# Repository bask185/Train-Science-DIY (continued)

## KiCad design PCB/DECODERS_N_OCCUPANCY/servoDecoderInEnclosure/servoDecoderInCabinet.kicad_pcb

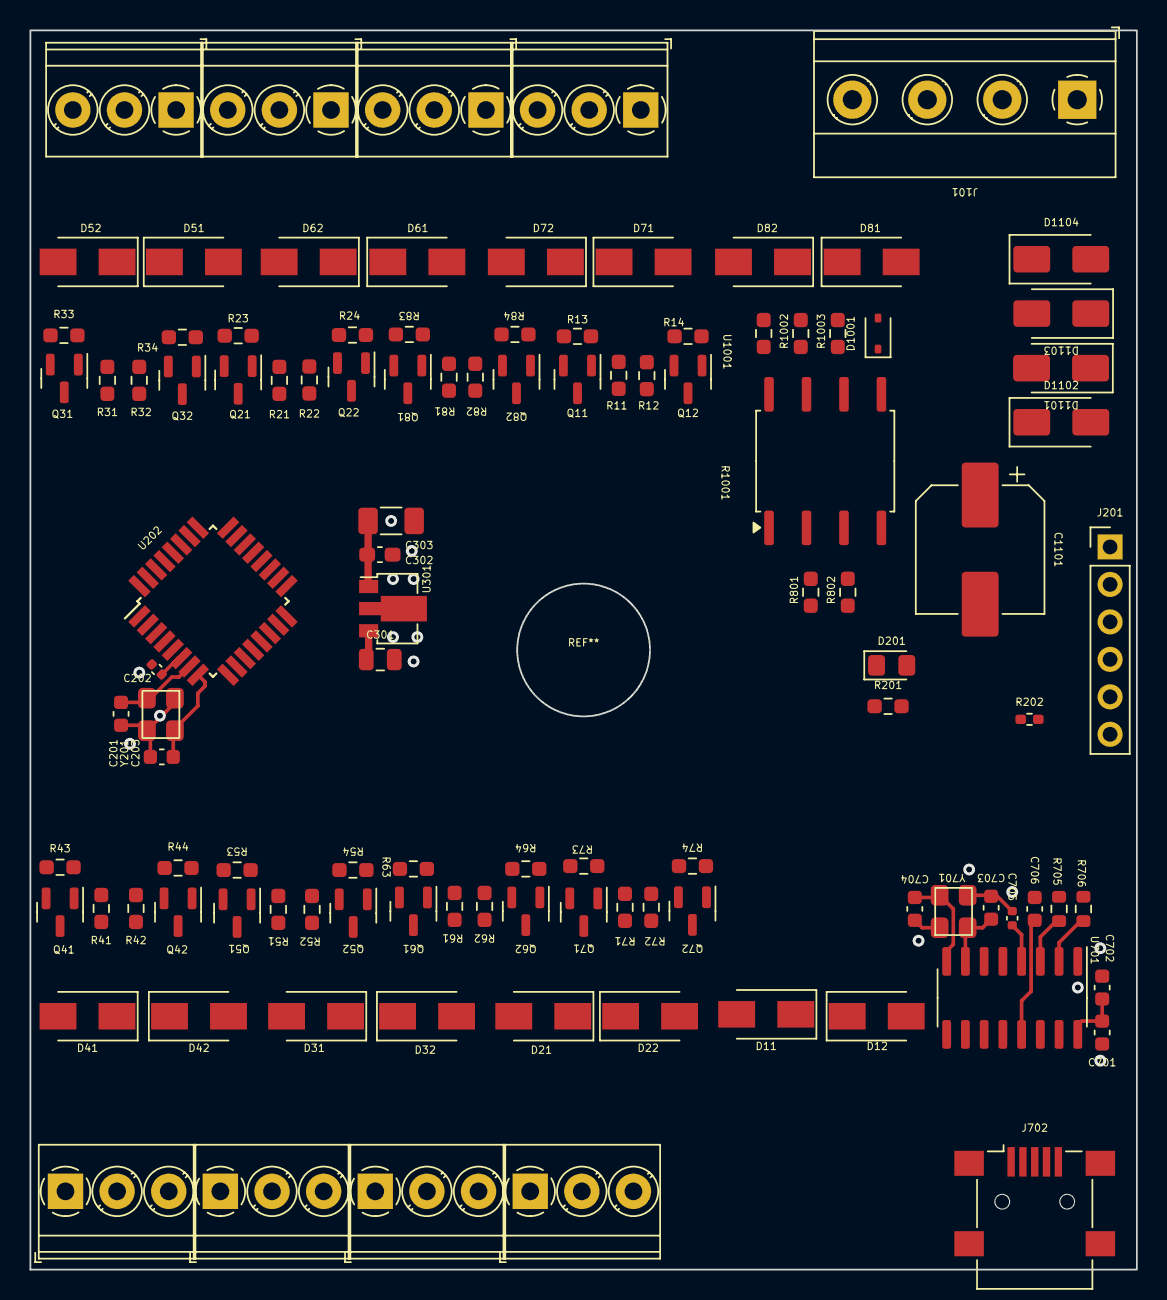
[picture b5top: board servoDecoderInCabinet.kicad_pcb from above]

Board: 2 copper layers, 75.0 x 84.0 mm, 101 parts (0 on the bottom side), 29 nets.

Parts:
C201, C203: 12pF; C_0603_1608Metric
C202, C705: 100nF; C_0402_1005Metric
C301: 470nF; C_0805_2012Metric
C302: 100nF; C_0603_1608Metric_Pad1.08x0.95mm_HandSolder
C303: 100uF; C_1206_3216Metric_Pad1.33x1.80mm_HandSolder
C701: 10uF; C_0603_1608Metric
C702, C706: 100nF; C_0603_1608Metric
C703, C704: 22pF; C_0603_1608Metric
C1101: 1000uF; CP_Elec_8x10.5
D11, D12, D21, D22, D31, D32, D41, D42, D51, D52, D61, D62, D71, D72, D81, D82: D_SMA
D201: LED; LED_0805_2012Metric_Pad1.15x1.40mm_HandSolder
D1001: 1N4148WS; D_SOD-323
D1101, D1102, D1103, D1104: SS53; D_SMA
J101: Screw_Terminal_01x04; TerminalBlock_Phoenix_MKDS-1,5-4-5.08_1x04_P5.08mm_Horizont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
J201: ICSP; PinHeader_1x06_P2.54mm_Vertical
J702: USB_B_Mini; USB_Mini-B_Lumberg_2486_01_Horizontal
Q11, Q12, Q21, Q22, Q31, Q32, Q41, Q42, Q51, Q52, Q61, Q62, Q71, Q72, Q81, Q82: SOT-23
R11, R12, R13, R14, R21, R22, R23, R24, R31, R32, R33, R34, R41, R42, R43, R44, R51, R52, R53, R54, R61, R62, R63, R64, R71, R72, R73, R74, R81, R82, R83, R84: R_0603_1608Metric_Pad0.98x0.95mm_HandSolder
R201: 6k2; R_0603_1608Metric_Pad0.98x0.95mm_HandSolder
R202: 10k; R_0402_1005Metric_Pad0.72x0.64mm_HandSolder
R705, R706: 1k; R_0603_1608Metric
R801, R802, R1002, R1003: 10k; R_0603_smalltext
R1001: 1k; R_0603_smalltext
U202: ATmega328-A; TQFP-32_7x7mm_P0.8mm
U301: L78L05_SOT89; SOT-89-3
U701: CH340G; SOIC-16_3.9x9.9mm_P1.27mm
U1001: 6N137; SOP-8_6.62x9.15mm_P2.54mm
Y201: Crystal_GND2; crystal_arduino
Y701: Crystal; crystal_arduino

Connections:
+5V: C202.1, C302.1, C303.1, C701.1, C702.1, J201.2, J702.1 (VBUS), R201.1, R202.2, R801.2, R802.2, R1002.1, R1003.1, U202.4 (VCC), U202.6 (VCC), U202.18 (AVCC), U301.1 (OUT), U701.16 (VCC), U1001.8 (VCC)
/A: J101.4, R1001.1
/B: D1001.2 (A), J101.3, U1001.3 (C)
/Buck/VCC: C301.1, C1101.1, D1101.1 (K), D1103.1 (K), U301.3 (IN)
/DCC/DCC_TTL: R1003.2, U202.32 (PD2), U1001.6 (VO)
/D_bridge/AC_1: D1101.2 (A), D1102.1 (K), J101.2
/D_bridge/AC_2: D1103.2 (A), D1104.1 (K), J101.1
/USB/Reset: C706.2, J201.6, R202.1, U202.29 (~RESET/PC6)
/USB/Rx: R705.2, U202.30 (PD0)
/USB/Tx: R706.1, U202.31 (PD1)
/atmega/LED: D201.1 (K), J201.3, U202.17 (PB5)
/atmega/X1: C201.2, U202.7 (XTAL1/PB6), Y201.1
/atmega/X2: C203.2, U202.8 (XTAL2/PB7), Y201.3
/atmega/bus2.pin1: R801.1, U202.11 (PD7)
/atmega/bus2.pin2: R802.1, U202.24 (PC1)
/atmega/sw3: J201.5, U202.15 (PB3)
/atmega/sw4: J201.4, U202.16 (PB4)
GND: C201.1, C202.2, C203.1, C301.2, C302.2, C303.2, C701.2, C702.2, C703.2, C704.2, C705.1, C1101.2, D1102.2 (A), D1104.2 (A), J201.1, J702.5 (GND), J702.6 (Shield), Q11.2 (S), Q12.2 (S), Q21.2 (S), Q22.2 (S), Q31.2 (S), Q32.2 (S), Q41.2 (S), Q42.2 (S), Q51.2 (S), Q52.2 (S), Q61.2 (S), Q62.2 (S), Q71.2 (S), Q72.2 (S), Q81.2 (S), Q82.2 (S), R13.1, R14.1, R23.1, R24.1, R33.1, R34.1, R43.1, R44.1, R53.1, R54.1, R63.1, R64.1, R73.1, R74.1, R83.1, R84.1, U202.3 (GND), U202.5 (GND), U202.21 (GND), U301.2 (GND), U701.1 (GND), U1001.5 (GND), Y201.2 (GND), Y201.4 (GND), Y701.2 (GND), Y701.4 (GND)
unnamed: D201.2 (A), R201.2
unnamed: D1001.1 (K), R1001.2, U1001.2 (A)
unnamed: J702.3 (D+), U701.5 (UD+)
unnamed: J702.2 (D-), U701.6 (UD-)
unnamed: R706.2, U701.3 (RXD)
unnamed: R705.1, U701.2 (TXD)
unnamed: C705.2, U701.4 (V3)
unnamed: C703.1, U701.7 (XI), Y701.1
unnamed: C704.1, U701.8 (XO), Y701.3
unnamed: C706.1, U701.13 (~DTR)
unnamed: R1002.2, U1001.7 (EN)

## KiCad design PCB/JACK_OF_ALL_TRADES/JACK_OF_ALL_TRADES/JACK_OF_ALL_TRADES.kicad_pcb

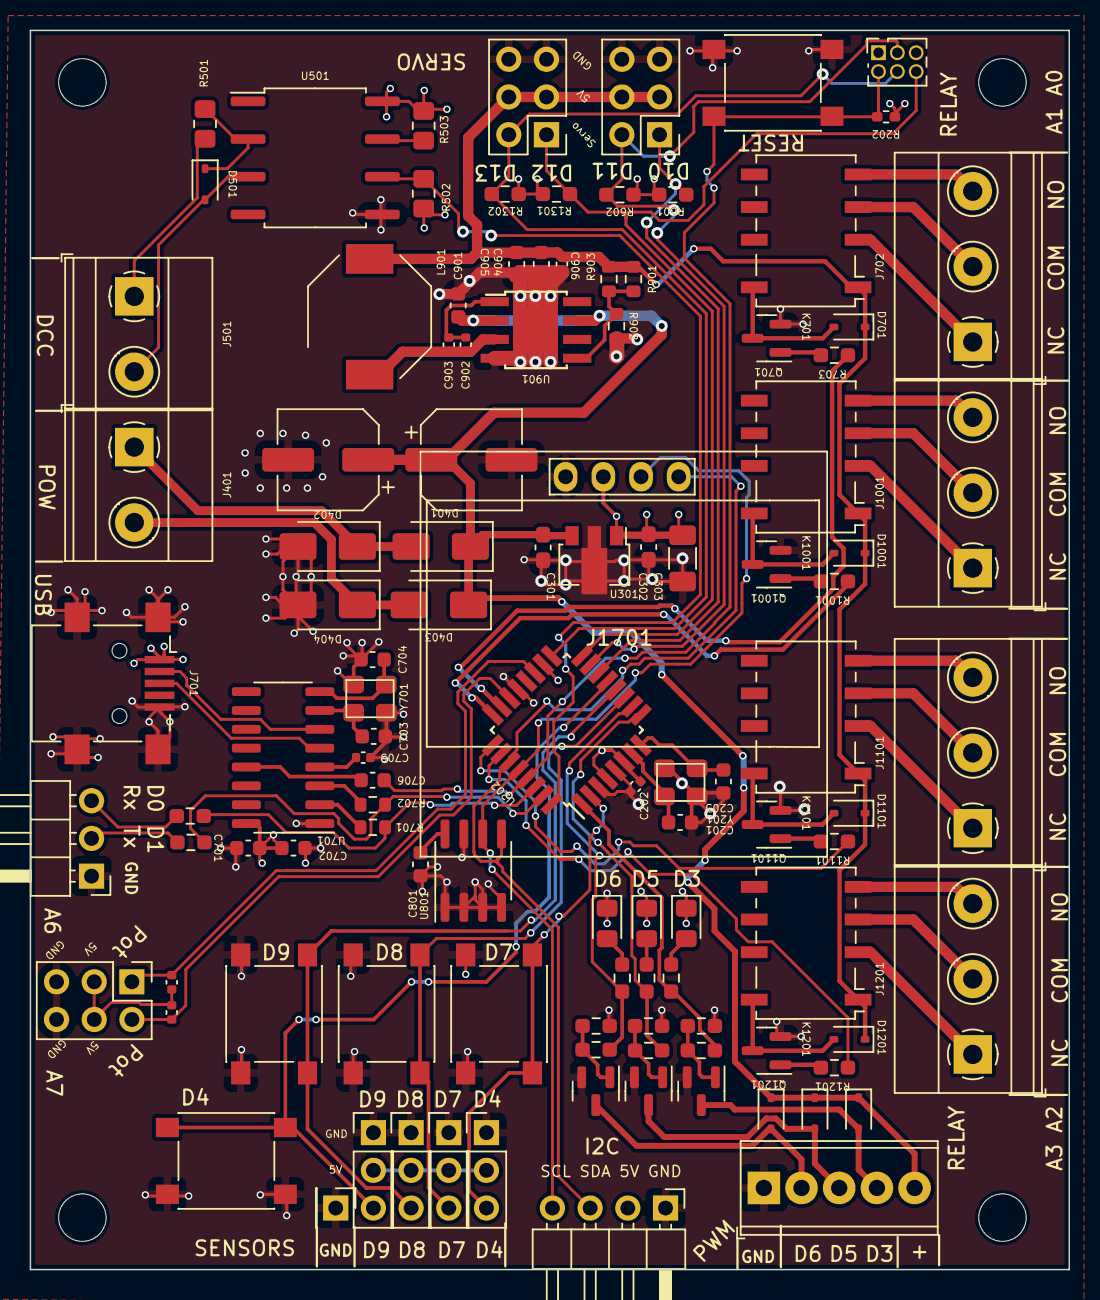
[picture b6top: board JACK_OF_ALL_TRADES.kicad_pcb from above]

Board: 4 copper layers, 70.0 x 83.5 mm, 111 parts (0 on the bottom side), 77 nets.

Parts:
C201, C203: 12pF; C_0603_1608Metric
C202, C705, C902, C906, C1401, C1402: 100nF; C_0402_1005Metric
C301: 330nF; C_0603_1608Metric_Pad1.08x0.95mm_HandSolder
C302: 100nF; C_0603_1608Metric_Pad1.08x0.95mm_HandSolder
C303: 100uF; C_1206_3216Metric_Pad1.33x1.80mm_HandSolder
C401, C402: 100uF; CP_Elec_6.3x5.8
C701: 10uF; C_0603_1608Metric
C702, C706, C801: 100nF; C_0603_1608Metric
C703, C704: 22pF; C_0603_1608Metric
C901, C904, C905: 22uF; C_0603_1608Metric
C903: 22nF; C_0402_1005Metric
D401, D402, D403, D404: SS53; D_SMA
D501, D701, D904, D905, D906, D1001, D1101, D1201: 1N4148WS; D_SOD-323
D901, D902, D903: LED; LED_0805_2012Metric_Pad1.15x1.40mm_HandSolder
J301: Conn_01x03_Pin; PinHeader_1x03_P2.54mm_Horizontal
J401, J501: Screw_Terminal_01x02; TerminalBlock_Phoenix_MKDS-1,5-2-5.08_1x02_P5.08mm_Horizont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
J601, J1301, J1401: Conn_02x03_Odd_Even; PinHeader_2x03_P2.54mm_Vertical
J701: USB_B_Mini; USB_Mini-B_Lumberg_2486_01_Horizontal
J702, J1001, J1101, J1201: Screw_Terminal_01x03; TerminalBlock_Phoenix_MKDS-1,5-3-5.08_1x03_P5.08mm_Horizont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
J802, J803, J804, J805: Conn_01x03_Pin; PinHeader_1x03_P2.54mm_Vertical
J806: Conn_01x01_Pin; PinHeader_1x01_P2.54mm_Vertical
J901: Screw_Terminal_01x05; TerminalBlock_Phoenix_MPT-0,5-5-2.54_1x05_P2.54mm_Horizontal
J1601: Conn_01x04_Pin; PinHeader_1x04_P2.54mm_Horizontal
J1701: Conn_01x04_Pin; 128x64OLED
K701, K1001, K1101, K1201: G6K-2F-Y-TR DC5; Relay_DPDT_Omron_G6K-2F-Y
L901: L; L_Bourns-SRU8028_8.0x8.0mm
Q701, Q1001, Q1101, Q1201: NPN_TOR; SOT-23
Q901, Q902, Q903: AO3400A; SOT-23
R202: 10k; R_0402_1005Metric_Pad0.72x0.64mm_HandSolder
R301, R302: 100R; R_0603_smalltext
R501: 1k; R_0805_2012Metric_Pad1.20x1.40mm_HandSolder
R502, R503: 10k; R_0805_2012Metric_Pad1.20x1.40mm_HandSolder
R601, R602, R1301, R1302: 10k; R_0603_smalltext
R701, R702: 1k; R_0603_1608Metric
R703, R1001, R1101, R1201: 1k; R_0603_smalltext
R901: 220k; R_0603_1608Metric
R902: 20k; R_0603_1608Metric
R903: 150k; R_0603_1608Metric
R904, R905, R906: 22R; R_0603_smalltext
R907, R908, R909: 3k3; R_0603_smalltext
R910, R911, R912: 22k; R_0603_smalltext
SW202, SW801, SW802, SW803, SW804: SW_Push; tactile_SMD_6mm
U201: HEADER_3x2; PinSocket_2x03_P1.27mm_Vertical
U202: ATmega328-A; TQFP-32_7x7mm_P0.8mm
U301: L78L05_SOT89; SOT-89-3
U501: 6N137; SOP-8_6.62x9.15mm_P2.54mm
U701: CH340G; SOIC-16_3.9x9.9mm_P1.27mm
U801: 24LC256; SOIC-8_3.9x4.9mm_P1.27mm
U901: MT2499A; TI_SO-PowerPAD-8
Y201: Crystal_GND2; crystal_arduino
Y701: Crystal; crystal_arduino

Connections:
+5V: C202.1, C302.1, C303.1, C701.1, C702.1, C801.2, C1401.1, C1402.2, J701.1 (VBUS), J802.2, J803.2, J804.2, J805.2, J1401.3, J1401.4, J1601.2, J1701.2, R202.1, R502.1, R503.1, R601.2, R602.2, R1301.2, R1302.2, U201.5, U202.4 (VCC), U202.6 (VCC), U202.18 (AVCC), U301.1 (OUT), U501.8 (VCC), U701.16 (VCC), U801.8 (VCC)
+5VA: C904.1, C905.1, C906.1, D701.1 (K), D1001.1 (K), D1101.1 (K), D1201.1 (K), J601.3, J601.4, J1301.3, J1301.4, K701.1, K1001.1, K1101.1, K1201.1, L901.2, R901.1, R903.2
/CPU/X1: C201.2, U202.7 (XTAL1/PB6), Y201.1
/CPU/X2: C203.2, U202.8 (XTAL2/PB7), Y201.3
/DCC: R503.2, U202.32 (PD2), U501.6 (VO)
/L1: R904.1, R907.2, U202.1 (PD3)
/L2: R905.1, R908.2, U202.9 (PD5)
/L3: R906.1, R909.2, U202.10 (PD6)
/P1: C1402.1, J1401.2, U202.22 (ADC7)
/P2: C1401.2, J1401.1, U202.19 (ADC6)
/R1: R703.1, U202.23 (PC0)
/R2: R1001.1, U202.24 (PC1)
/R3: R1101.1, U202.25 (PC2)
/R4: R1201.1, U202.26 (PC3)
/Rx: R301.2, R701.2, U202.30 (PD0)
/S1: J601.1, R601.1, U202.14 (PB2)
/S2: J601.2, R602.1, U201.3, U202.15 (PB3)
/S3: J1301.1, R1301.1, U201.6, U202.16 (PB4)
/S4: J1301.2, R1302.1, U201.4, U202.17 (PB5)
/SCL: J1601.4, J1701.3, U202.28 (PC5), U801.6 (SCL)
/SDA: J1601.3, J1701.4, U202.27 (PC4), U801.5 (SDA)
/SW1: J802.3, SW801.1, U202.2 (PD4)
/SW2: J803.3, SW802.1, U202.11 (PD7)
/SW3: J804.3, SW803.1, U202.12 (PB0)
/SW4: J805.3, SW804.1, U202.13 (PB1)
/Tx: R302.2, R702.1, U202.31 (PD1)
/reset: C706.2, R202.2, SW202.2, U201.2, U202.29 (~RESET/PC6)
GND: C201.1, C202.2, C203.1, C301.2, C302.2, C303.2, C401.2, C402.2, C701.2, C702.2, C703.2, C704.2, C705.1, C801.1, C901.2, C904.2, C905.2, C906.2, D402.2 (A), D404.2 (A), D901.1 (K), D902.1 (K), D903.1 (K), J301.1, J601.5, J601.6, J701.5 (GND), J701.6 (Shield), J802.1, J803.1, J804.1, J805.1, J806.1, J901.1, J1301.5, J1301.6, J1401.5, J1401.6, J1601.1, J1701.1, Q701.2 (E), Q901.2 (S), Q902.2 (S), Q903.2 (S), Q1001.2 (E), Q1101.2 (E), Q1201.2 (E), R902.2, R910.2, R911.2, R912.2, SW202.1, SW801.2, SW802.2, SW803.2, SW804.2, U201.1, U202.3 (GND), U202.5 (GND), U202.21 (GND), U301.2 (GND), U501.5 (GND), U701.1 (GND), U801.1 (A0), U801.2 (A1), U801.3 (A2), U801.4 (GND), U801.7 (WP), U901.4 (GND), U901.9 (GND), Y201.2 (GND), Y201.4 (GND), Y701.2 (GND), Y701.4 (GND)
unnamed: D401.2 (A), D402.1 (K), J401.1
unnamed: D403.2 (A), D404.1 (K), J401.2
unnamed: D501.2 (A), J501.2, U501.3 (C)
unnamed: D501.1 (K), R501.2, U501.2 (A)
unnamed: D701.2 (A), K701.8, Q701.3 (C)
unnamed: D901.2 (A), R907.1
unnamed: D902.2 (A), R908.1
unnamed: D903.2 (A), R909.1
unnamed: D904.2 (A), J901.4, Q901.3 (D)
unnamed: D905.2 (A), J901.3, Q902.3 (D)
unnamed: D906.2 (A), J901.2, Q903.3 (D)
unnamed: D1001.2 (A), K1001.8, Q1001.3 (C)
unnamed: D1101.2 (A), K1101.8, Q1101.3 (C)
unnamed: D1201.2 (A), K1201.8, Q1201.3 (C)
unnamed: J301.2, R302.1
unnamed: J301.3, R301.1
unnamed: J501.1, R501.1
unnamed: J701.3 (D+), U701.5 (UD+)
unnamed: J701.2 (D-), U701.6 (UD-)
unnamed: J702.1, K701.2
unnamed: J702.2, K701.3
unnamed: J702.3, K701.4
unnamed: J1001.1, K1001.2
unnamed: J1001.2, K1001.3
unnamed: J1001.3, K1001.4
unnamed: J1101.1, K1101.2
unnamed: J1101.2, K1101.3
unnamed: J1101.3, K1101.4
unnamed: J1201.1, K1201.2
unnamed: J1201.2, K1201.3
unnamed: J1201.3, K1201.4
unnamed: Q701.1 (B), R703.2
unnamed: Q901.1 (G), R904.2, R910.1
unnamed: Q902.1 (G), R905.2, R911.1
unnamed: Q903.1 (G), R906.2, R912.1
unnamed: Q1001.1 (B), R1001.2
unnamed: Q1101.1 (B), R1101.2
unnamed: Q1201.1 (B), R1201.2
unnamed: R502.2, U501.7 (EN)
unnamed: R702.2, U701.3 (RXD)
unnamed: R701.1, U701.2 (TXD)
unnamed: C705.2, U701.4 (V3)
unnamed: C703.1, U701.7 (XI), Y701.1
unnamed: C704.1, U701.8 (XO), Y701.3
unnamed: C706.1, U701.13 (~DTR)
unnamed: C902.1, C903.1, U901.1 (BS)
unnamed: R901.2, R902.1, R903.1, U901.5 (FB)
unnamed: C902.2, C903.2, L901.1, U901.3 (SW)
VCC: C301.1, C401.1, C402.1, C901.1, D401.1 (K), D403.1 (K), D904.1 (K), D905.1 (K), D906.1 (K), J901.5, U301.3 (IN), U901.2 (Vin), U901.7 (EN)
